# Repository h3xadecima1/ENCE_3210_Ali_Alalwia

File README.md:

Title: Microprocessor1 Lab
Date Created : 01/10/2025

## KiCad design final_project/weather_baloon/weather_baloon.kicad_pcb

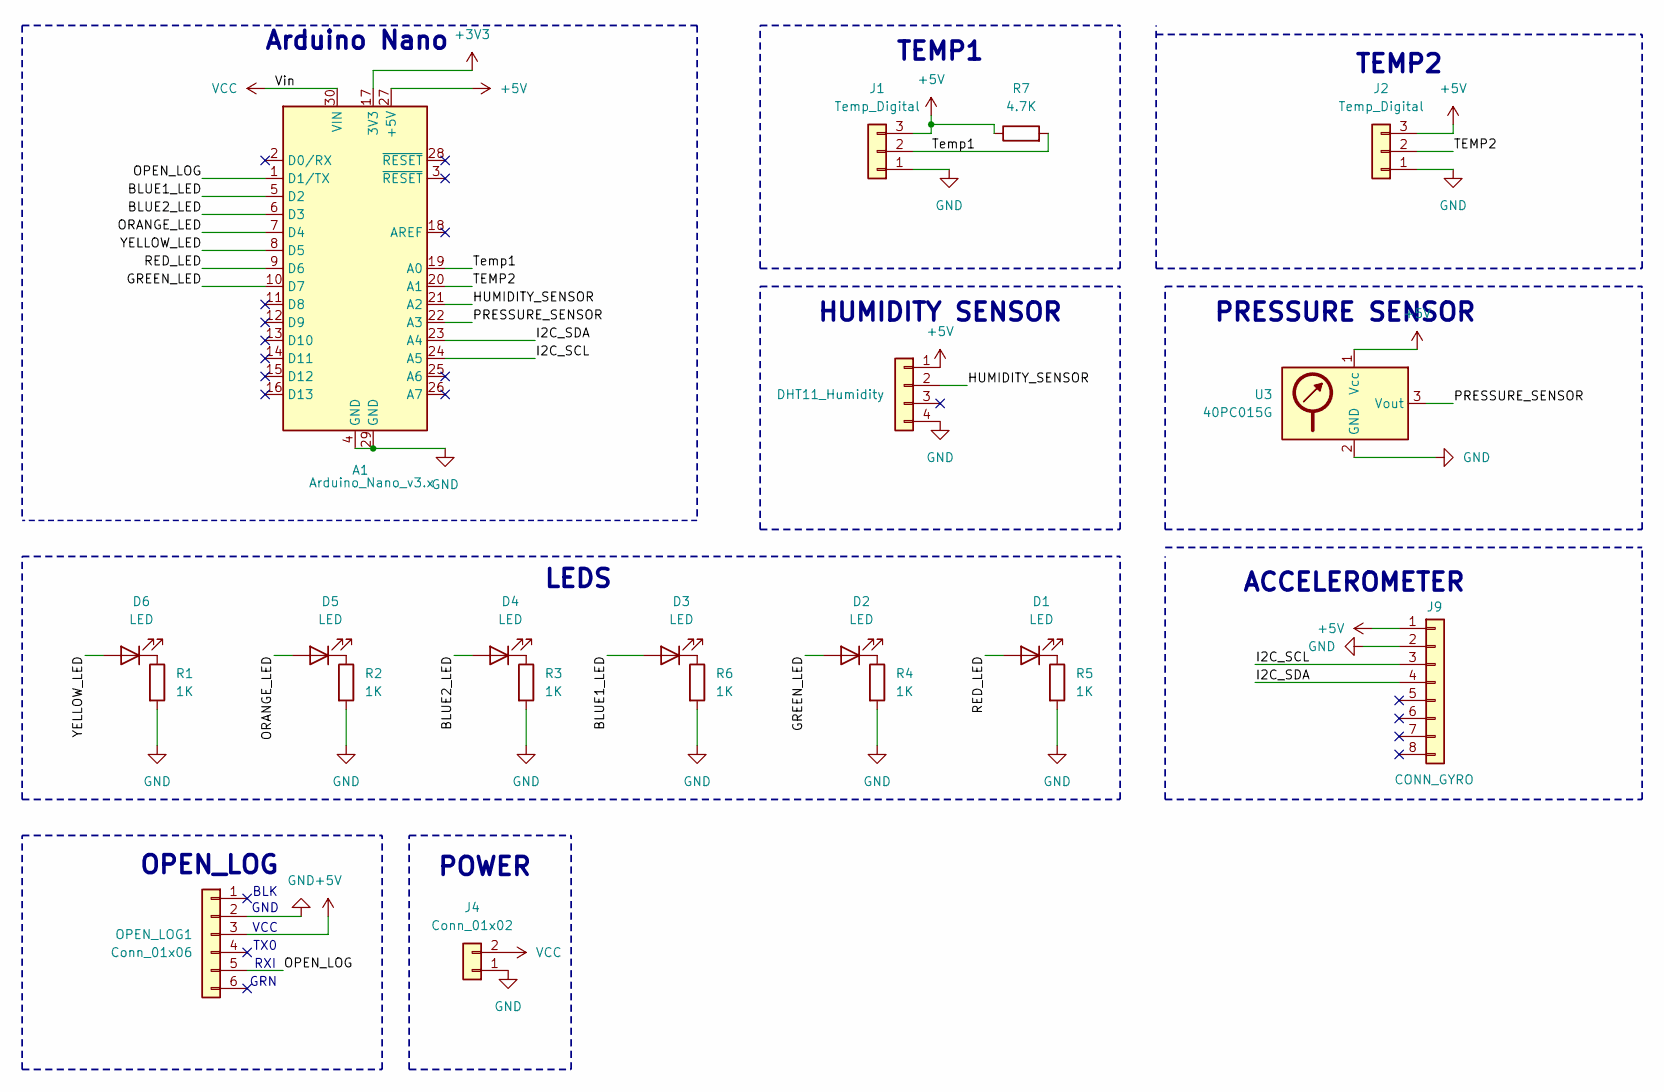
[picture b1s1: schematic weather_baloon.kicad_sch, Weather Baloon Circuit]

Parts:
A1: Arduino_Nano_v3.x; Arduino_Nano
D1, D2, D3, D6: LED; LED_D5.0mm
D4, D5: LED; PinSocket_1x02_P2.54mm_Vertical
J1: Temp_Digital; JST_XH_B3B-XH-A_1x03_P2.50mm_Vertical
J2: Temp_Digital; XDCR_TMP36GT9
J3: DHT11_Humidity; PinSocket_1x04_P2.54mm_Vertical
J4: Conn_01x02; JST_XH_B2B-XH-A_1x02_P2.50mm_Vertical
J9: CONN_GYRO; PinSocket_1x08_P2.54mm_Vertical
OPEN_LOG1: Conn_01x06; PinHeader_1x06_P2.54mm_Vertical
R1, R2, R3, R4, R5, R6: 1K; R_Axial_DIN0207_L6.3mm_D2.5mm_P10.16mm_Horizontal
R7: 4.7K; R_Axial_DIN0207_L6.3mm_D2.5mm_P10.16mm_Horizontal
U3: 40PC015G; DIP1330W46P254L1000H544Q8

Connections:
+3V3: A1.17 (3V3)
+5V: A1.27 (+5V), J1.3, J2.3, J3.1, J9.1, OPEN_LOG1.3, R7.1, U3.1 (Vcc)
/BLUE1_LED: A1.5 (D2), D3.2 (A)
/BLUE2_LED: A1.6 (D3), D4.2 (A)
/GREEN_LED: A1.10 (D7), D2.2 (A)
/HUMIDITY_SENSOR: A1.21 (A2), J3.2
/I2C_SCL: A1.24 (A5), J9.3
/I2C_SDA: A1.23 (A4), J9.4
/OPEN_LOG: A1.1 (D1/TX), OPEN_LOG1.5
/ORANGE_LED: A1.7 (D4), D5.2 (A)
/PRESSURE_SENSOR: A1.22 (A3), U3.3 (Vout)
/RED_LED: A1.9 (D6), D1.2 (A)
/TEMP2: A1.20 (A1), J2.2
/Temp1: A1.19 (A0), J1.2, R7.2
/YELLOW_LED: A1.8 (D5), D6.2 (A)
GND: A1.4 (GND), A1.29 (GND), J1.1, J2.1, J3.4, J4.1, J9.2, OPEN_LOG1.2, R1.2, R2.2, R3.2, R4.2, R5.2, R6.2, U3.2 (GND)
unnamed: D1.1 (K), R5.1
unnamed: D2.1 (K), R4.1
unnamed: D3.1 (K), R6.1
unnamed: D4.1 (K), R3.1
unnamed: D5.1 (K), R2.1
unnamed: D6.1 (K), R1.1
VCC: A1.30 (VIN), J4.2

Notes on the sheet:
GND
Arduino Nano
LEDS
RXI
POWER
TX0
ACCELEROMETER
OPEN_LOG
VCC
HUMIDITY SENSOR
PRESSURE SENSOR
GRN
TEMP2
TEMP1
BLK

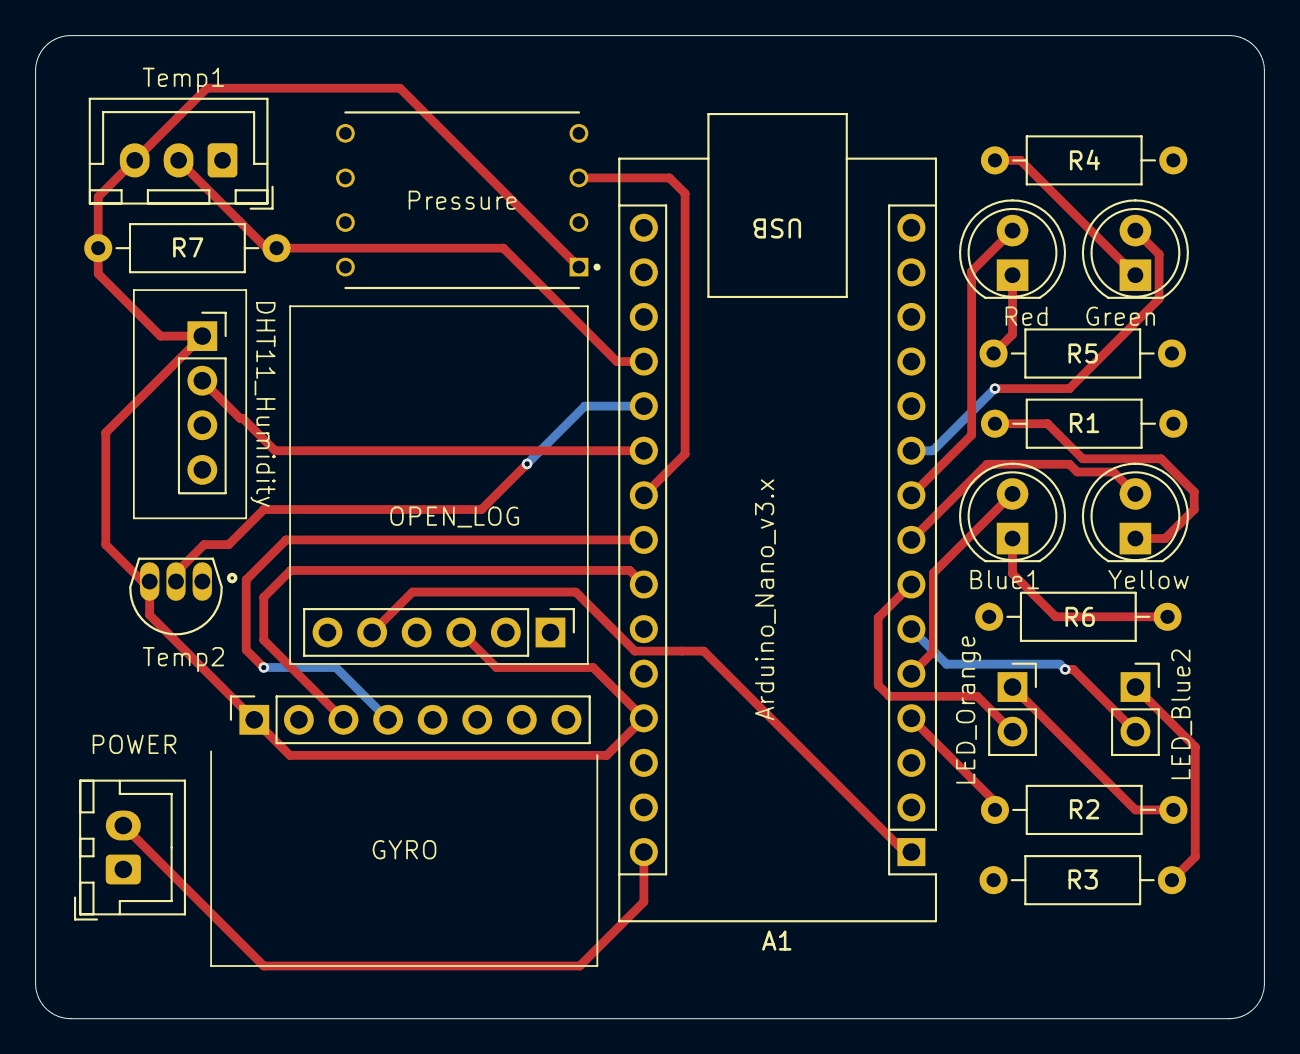
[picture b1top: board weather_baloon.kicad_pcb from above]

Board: 2 copper layers, 70.0 x 56.0 mm, 21 parts (0 on the bottom side), 22 nets.

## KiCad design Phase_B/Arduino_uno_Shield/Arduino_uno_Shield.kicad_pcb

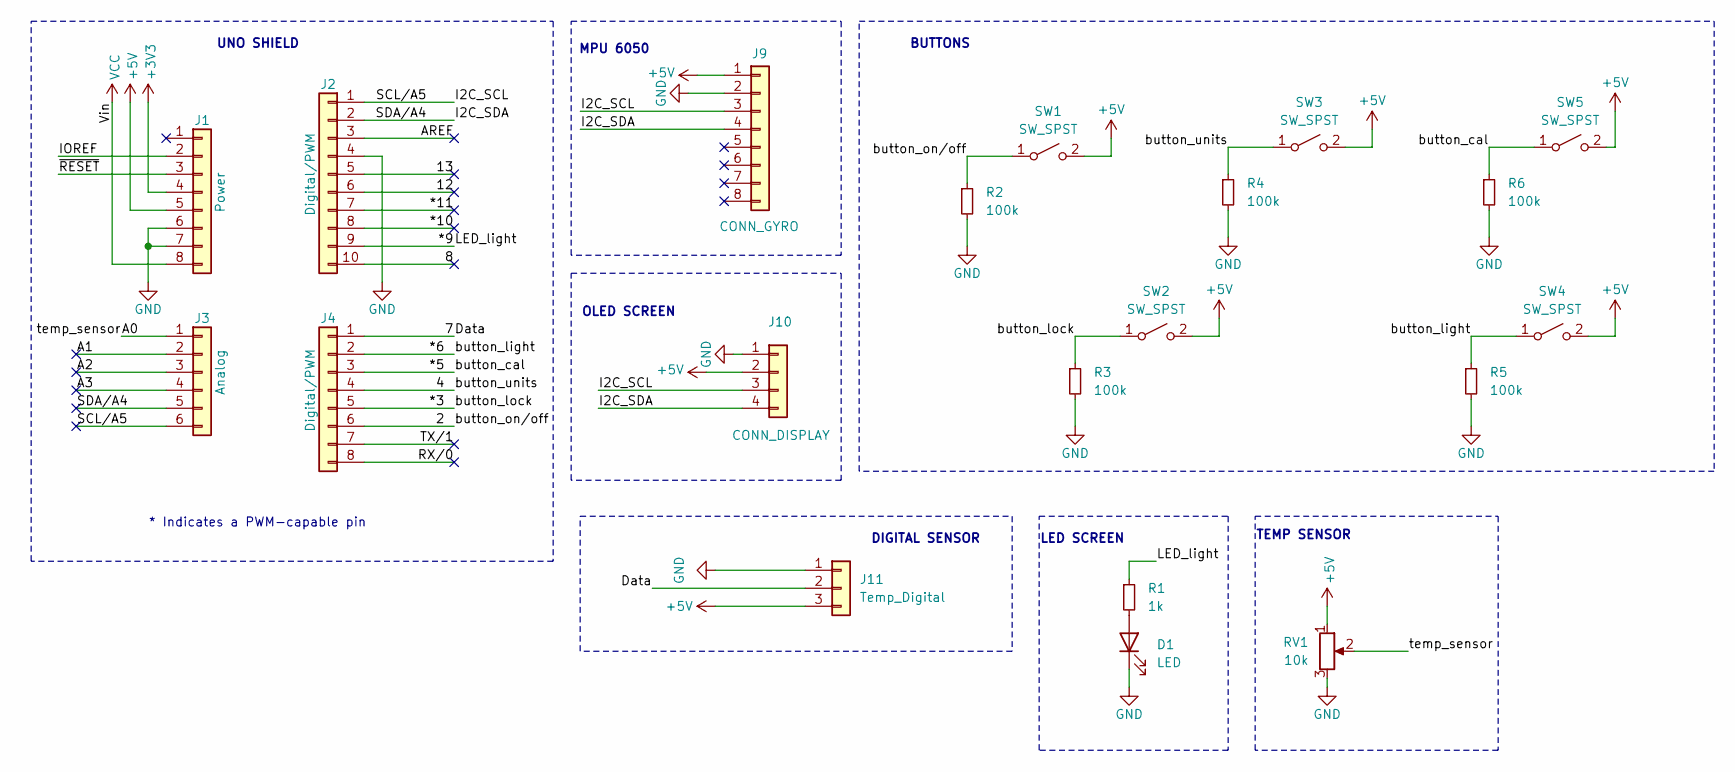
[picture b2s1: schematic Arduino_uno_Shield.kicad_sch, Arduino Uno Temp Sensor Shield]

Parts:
D1: LED; LED_D5.0mm
J1: Power; PinSocket_1x08_P2.54mm_Vertical
J2: Digital/PWM; PinSocket_1x10_P2.54mm_Vertical
J3: Analog; PinSocket_1x06_P2.54mm_Vertical
J4: Digital/PWM; PinSocket_1x08_P2.54mm_Vertical
J9: CONN_GYRO; PinSocket_1x08_P2.54mm_Vertical
J10: CONN_DISPLAY; PinSocket_1x04_P2.54mm_Vertical
J11: Temp_Digital; JST_XH_B3B-XH-A_1x03_P2.50mm_Vertical
R1: 1k; R_Axial_DIN0207_L6.3mm_D2.5mm_P10.16mm_Horizontal
R2, R3, R4, R5, R6: 100k; R_Axial_DIN0207_L6.3mm_D2.5mm_P10.16mm_Horizontal
RV1: 10k; Potentiometer_Bourns_3386P_Vertical
SW1, SW2, SW3, SW4, SW5: SW_SPST; SW_PUSH_6mm

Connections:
+3V3: J1.4
+5V: J1.5, J9.1, J10.2, J11.3, RV1.1, SW1.2 (B), SW2.2 (B), SW3.2 (B), SW4.2 (B), SW5.2 (B)
/2: J4.6, R2.1, SW1.1 (A)
/4: J4.4, R4.1, SW3.1 (A)
/7: J4.1, J11.2
/8: J2.10
/12: J2.6
/13: J2.5
/*3: J4.5, R3.1, SW2.1 (A)
/*5: J4.3, R6.1, SW5.1 (A)
/*6: J4.2, R5.1, SW4.1 (A)
/*9: J2.9, R1.1
/*10: J2.8
/*11: J2.7
/A0: J3.1, RV1.2
/A1: J3.2
/A2: J3.3
/A3: J3.4
/AREF: J2.3
/I2C_SCL: J2.1, J3.6, J9.3, J10.3
/I2C_SDA: J2.2, J3.5, J9.4, J10.4
/IOREF: J1.2
/RX/0: J4.8
/TX/1: J4.7
/~RESET: J1.3
GND: D1.1 (K), J1.6, J1.7, J2.4, J9.2, J10.1, J11.1, R2.2, R3.2, R4.2, R5.2, R6.2, RV1.3
unnamed: D1.2 (A), R1.2
VCC: J1.8

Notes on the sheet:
OLED SCREEN
MPU 6050
BUTTONS
* Indicates a PWM-capable pin
TEMP SENSOR
DIGITAL SENSOR
UNO SHIELD
LED SCREEN

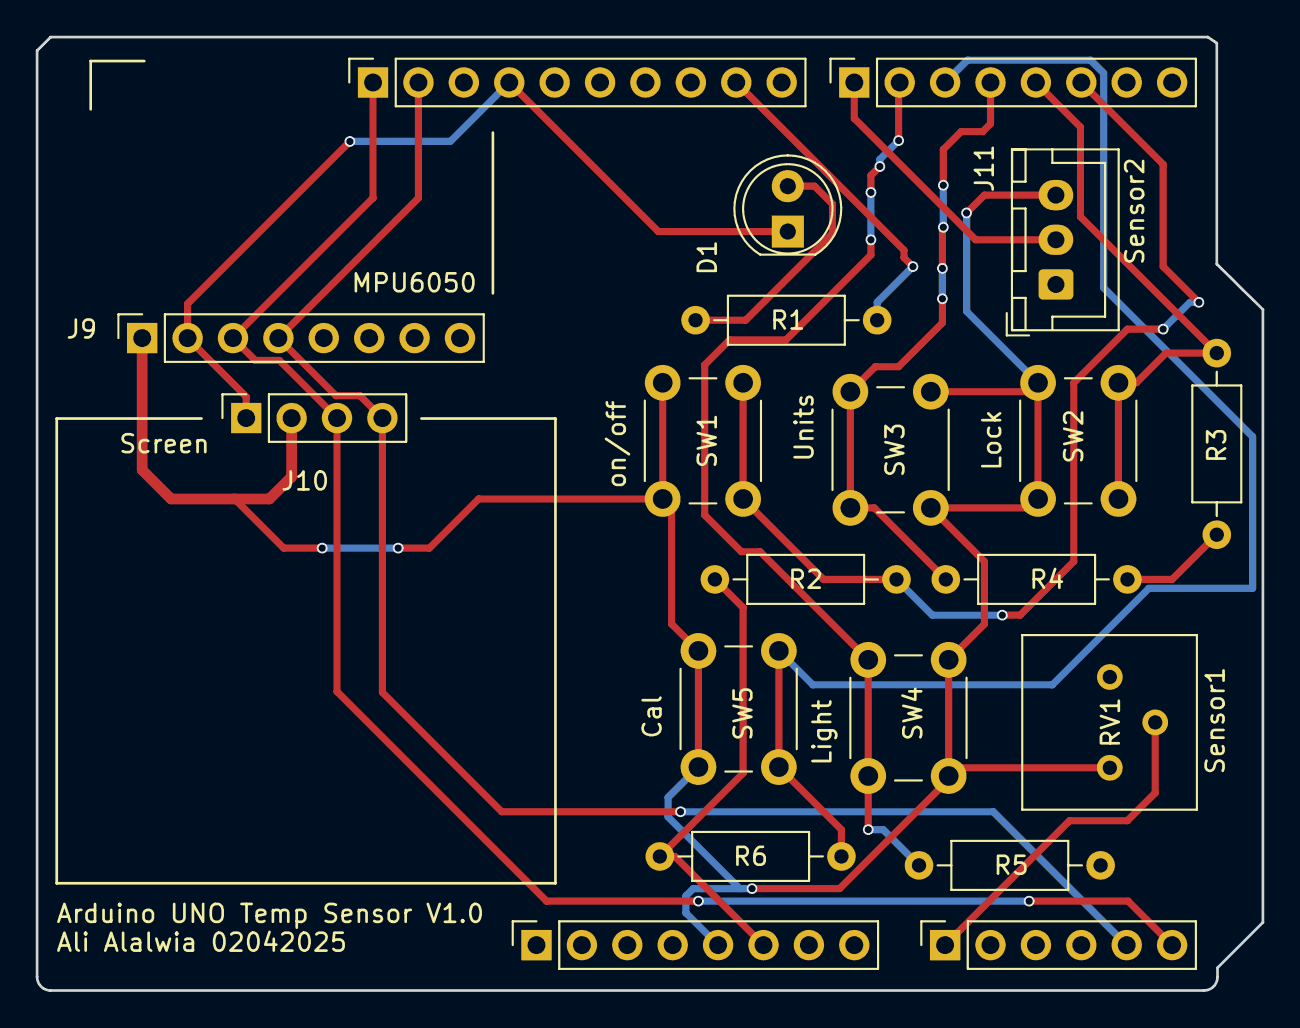
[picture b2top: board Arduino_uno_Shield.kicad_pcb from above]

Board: 2 copper layers, 68.6 x 53.3 mm, 20 parts (0 on the bottom side), 13 nets.

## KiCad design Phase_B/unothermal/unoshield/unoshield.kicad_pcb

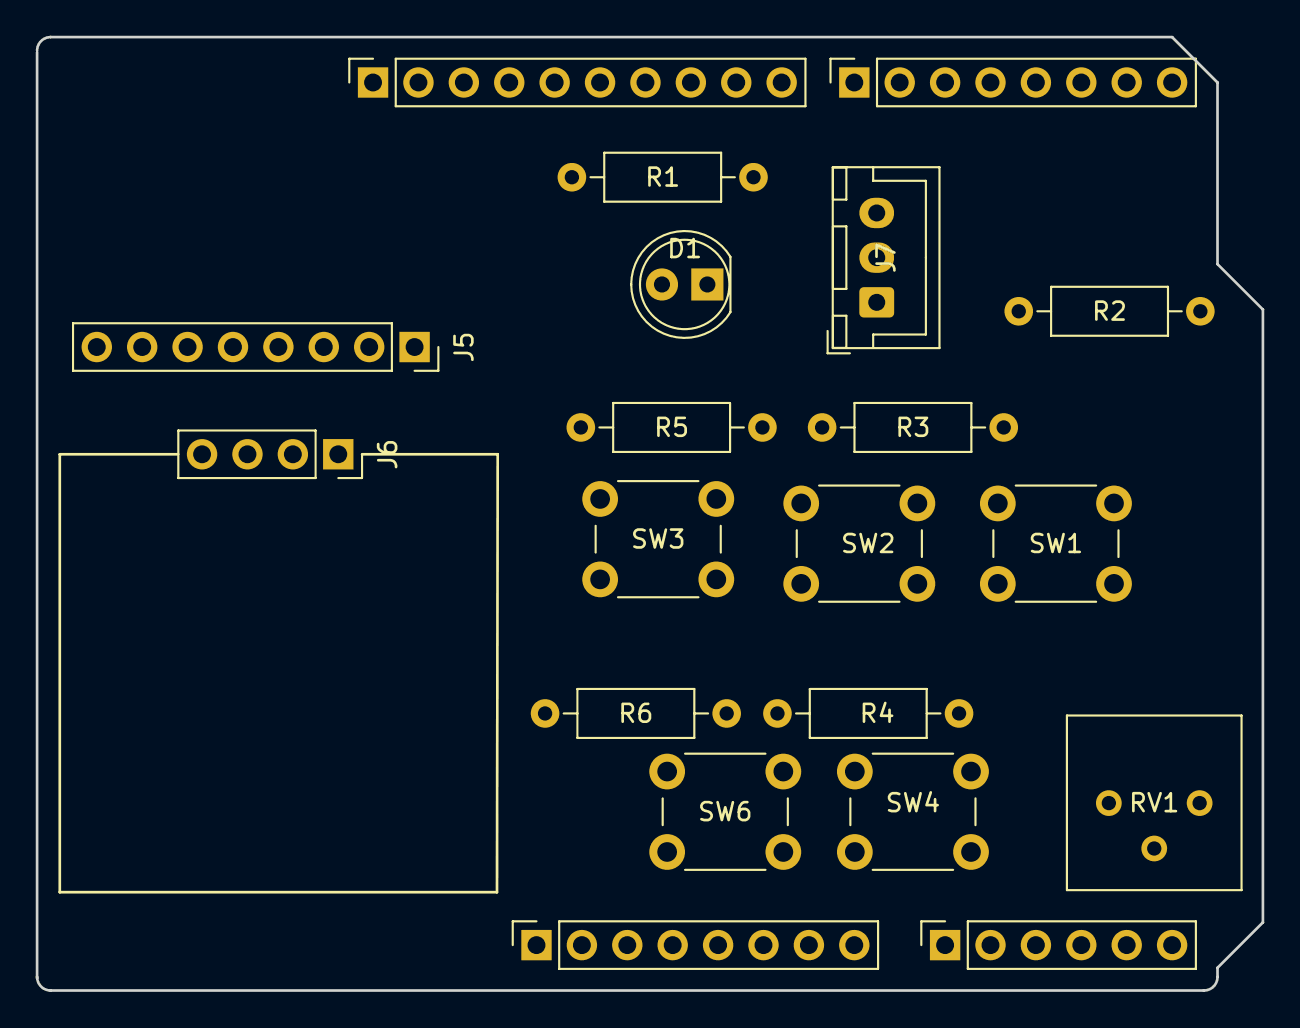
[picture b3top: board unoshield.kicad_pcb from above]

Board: 2 copper layers, 68.6 x 53.3 mm, 20 parts (0 on the bottom side), 10 nets, no tracks yet.

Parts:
D1: LED; LED_D5.0mm
J1: Power; PinSocket_1x08_P2.54mm_Vertical
J2: Digital/PWM; PinSocket_1x10_P2.54mm_Vertical
J3: Analog; PinSocket_1x06_P2.54mm_Vertical
J4: Digital/PWM; PinSocket_1x08_P2.54mm_Vertical
J5: CONN_GYRO; PinSocket_1x08_P2.54mm_Vertical
J6: Conn_01x04; PinSocket_1x04_P2.54mm_Vertical
J7: Temp_Digital; JST_XH_B3B-XH-A_1x03_P2.50mm_Vertical
R1, R2, R3, R4, R5, R6: R; R_Axial_DIN0207_L6.3mm_D2.5mm_P10.16mm_Horizontal
RV1: R_Potentiometer; Potentiometer_Bourns_3386P_Vertical
SW1, SW2, SW3, SW4, SW6: SW_DPST_x2; SW_PUSH_6mm

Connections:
+5V: J1.5, J5.1, J6.2, J7.3, R6.1, RV1.1
/I2C_SCL: J2.1, J5.3, J6.4
/I2C_SDA: J2.2, J5.4
GND: D1.1 (K), J1.6, J1.7, J2.4, J5.2, J6.1, J7.1, R1.1, R2.1, R3.1, R4.1, R5.1, RV1.3
unnamed: D1.2 (A), R6.2
unnamed: R1.2, SW1.1 (A)
unnamed: R2.2, SW2.1 (A)
unnamed: R3.2, SW3.1 (A)
unnamed: R4.2, SW4.1 (A)
unnamed: R5.2, SW6.1 (A)

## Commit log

2025-01-10 Lab1
2025-01-10 README.md
2025-01-24 Lab2 Update
2025-01-26 Lab3 Update
2025-01-31 Phase_B
2025-02-19 Phase_C
2025-02-26 Add files via upload
    Circuit Block Diagram
2025-02-28 Lab4
2025-03-07 finl_project
2025-03-08 final_project
